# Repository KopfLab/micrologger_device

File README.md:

# *µLogger*

This repository holds the code, schematics, and documentation to build a ***M**odular **I**nternet **C**ontrollable **R**eal-time **O**ptical-density Logger* (***microLogger*** or ***µLogger*** for short). All content of this repository is free to use for noncommercial research and development efforts as outlined in the terms of the included [LICENSE file](LICENSE.md).

To cite ***µLogger*** in publications use:

> Kopf S and Younkin A, 2025. _µLogger: a Modular Internet Controllable Real-time Optical-density Logger_. <https://github.com/KopfLab/micrologger_device>

A BibTeX entry for LaTeX users is

```
@Manual{
  microLogger,
  title = {µLogger: a Modular Internet Controllable Real-time Optical-density Logger},
  author = {Sebastian Kopf and Adam Younkin},
  year = {2025},
  url = {https://github.com/KopfLab/micrologger_device}
}
```

## About

Modular Internet Controllable Real-time Optical-density Loggers (µLoggers) are optical density measurement devices for continuously recording the growth of a microbial culture directly in its culturing vessel. Each microLogger consists of a compact high strength carbon fibre culture vessel holder that has a built-in light source at a narrow band wavelength and a light sensor with automatically adjustable gain that measures the light transmission across the culture vessel to automatically and continuously quantify optical density at user defined time intervals. A magnetically coupled stirrer built into the vessel holder can agitate the culture both continuously as well as in vortexing mode  (= pulse agitation) at user-set stir/vortexing speeds from 50 to 5000 rpm. Culture vessel adapters that are magnetically secured to the vessel holder allow for quick and easy swapping for differently sized culture vessels and snugly hold the culture vessel in place using a radial spring mechanism. Adapters can be custom sized for the preferred culture vessel from standard 18mm diameter 15mL culture tubes up to 58mm GL45 100mL media bottles. Typical adapter sizes also cover culture vessels typically used in anaerobic microbial culture including balch tubes and serum bottles of varying sizes. Additional optional adapters that are magnetically secured on top of the vessel adapter can provide additional functionality such as user-controlled illumination for experiments with phototrophic microorganisms. Each µLogger is connected to a compact controller (the micrologger "brain") that connects to the culture vessel holder via a single cable such that the vessel holder can be placed inside an incubator (e.g. for temperature or gas modulation) while the controller sits outside the incubator and provides full control and power to the culture vessel holder for stirring, optical density measurements, and (optionally) lighting. The controller has built-in WiFi connectivity and receives/sends data wirelessly wirelessly. This makes it possible to monitor optical density of the microbial cultures in real-time from any location. The controller also has a built-in screen that displays the state of the micrologger (e.g. stir speed, read interval, internet connectivity) as well as the real-time data from the culture vessel so that users can check on their experiments with a glance at the controller without opening the incubator and without handling the culture vessel in any way to avoid potentially disturbing an experiment. For convenience, the controller can also be attached magnetically to the outside of the incubator (if metal) or any other metallic surface.

## Features

- **Continuous optical-density logging** — a narrow-band beam LED and an OPT101 photodetector with automatically optimized amplifier gain measure the light transmission across the culture vessel; the firmware computes optical density (−log₁₀ of transmittance) at user-defined intervals, propagates a standard-deviation error onto every reading, and stores the per-vessel zero reference on the device so it survives power outages.
- **Magnetic stirring & vortexing** — a built-in brushless motor drives a magnetically coupled stirrer with configurable speed, acceleration/deceleration ramps, and a vortex (pulse-agitation) mode; stirring can automatically pause or vortex around each optical-density read.
- **Swappable, magnetically secured vessel adapters** — 3D-printed adapters hold vessels from 18 mm / 15 mL culture tubes up to GL45 100 mL bottles (including Balch/Hungate tubes and serum bottles) with a radial spring mechanism, and accept stacking add-ons such as the illumination adapter.
- **Optional illumination for phototrophs** — a dimmable light adapter with permanent on/off or scheduled (repeating daily-cycle) operation and a light-synced cooling fan.
- **Temperature & power monitoring** — on-board TMP117 temperature sensing at the vessel holder plus supply-voltage monitoring with under-voltage warnings on the display.
- **At-a-glance local display** — the WiFi controller sits outside the incubator, links to the reader over a single cable, and shows live optical density, stir speed, temperature, connectivity, and publishing status on an OLED; it mounts magnetically to any metal surface.
- **Real-time cloud connectivity** — built on the Particle [Photon 2](https://docs.particle.io/reference/datasheets/wi-fi/photon-2-datasheet/); publishes JSON data logs via cloud webhooks (the `microloggerData` event) for recording into spreadsheets or databases, averages data over configurable intervals, and caches logs during offline periods to bridge device downtime.
- **Self-describing & remotely controllable** — the entire device state is exposed as a self-describing data structure (SDDS) that the [sddsParticle](https://github.com/KopfLab/sddsParticle) web GUI (or the Particle CLI/API) can browse and control, with persisted settings, one-shot actions, and per-variable publish intervals.
- **Open & modular** — component-based, easily extensible C++ firmware (separate `sensor`, `stirrer`, `lights`, and `environment` components), open [KiCad](https://www.kicad.org/) hardware, and open [OpenSCAD](https://openscad.org/) 3D-printable mechanical parts.

## Hardware

A µLogger is built from four custom circuit boards, designed in [KiCad](https://www.kicad.org/) with sources under [`pcbs/`](pcbs). For each board the board layout is shown below (click it to open the full schematic / wiring diagram as a PDF).

### Controller board — the µLogger "brain"

A Particle Photon 2 for WiFi and control, the OLED status display, the 24 V power input with supply-voltage monitoring, the controller-version code pins, and the single-cable connector to the reader (the vessel holder).

*→ [Controller board wiring diagram (PDF)](pcbs/controller_board/controller_board.pdf)*

### Sensor board

Mounted in the vessel holder: the OPT101 photodiode/transimpedance amplifier with a two-stage digital-potentiometer gain circuit (MCP4017 + AD5246), the TCA9534 I2C IO expander (reader-connection detection plus beam and indicator LEDs), and the measurement-beam LED. The board version is read back over the IO expander.

*→ [Sensor board wiring diagram (PDF)](pcbs/sensor_board/sensor_board.pdf)*

### LED board

The optional illumination adapter: the light LEDs driven by a PCA9633 PWM controller for dimming, together with the cooling fan.

*→ [LED board wiring diagram (PDF)](pcbs/led_board/led_board.pdf)*

### Temperature board

A simple TMP117 precision temperature sensor placed at the vessel holder.

*→ [Temperature board wiring diagram (PDF)](pcbs/temperature_board/temperature_board.pdf)*

## 3D printed parts

The vessel holder, stirrer, controller enclosure, and all vessel adapters are 3D-printable. The STL files live in [`prints/stl/`](prints/stl) and the parametric source models are the [OpenSCAD](https://openscad.org/) files [`prints/micrologger_device.scad`](prints/micrologger_device.scad) and [`prints/micrologger_controller.scad`](prints/micrologger_controller.scad). File names ending in `_nozzle_0.4mm` are optimized for a 0.4 mm printer nozzle.

The parts fall into a few groups:

- **Device body & stirrer** — the high-strength vessel-holder body (`micrologger_device_*`, designed to be printed in carbon-fibre-reinforced filament) that houses the sensor/beam optics, and the magnetically coupled `micrologger_stirrer_*`.
- **Vessel adapters** — magnetically secured, radially sprung adapters sized for specific culturing vessels: `balch`, `hungate`, `culture60`, `gl45`, `serum60`/`serum120`/`serum160`, plus the `base_*` adapters that go into the base of the vessel holder for small vial sizes.
- **Light adapters** — `micrologger_light_adapter_up`/`_down` for the optional illumination add-on.
- **Controller enclosure** — `micrologger_controller_body`, `micrologger_controller_back`, and `micrologger_controller_magnet_holder` for the "brain" controller box.

👉 See [**`prints/README.md`**](prints/README.md) for the complete list of all printable parts with rendered previews.

## Building, flashing & monitoring

The firmware is written for the Particle Photon 2 (platform `p2`) and built with the [Particle Cloud command line interface (CLI)](https://github.com/spark/particle-cli). Builds are driven by Ruby [Rake](https://ruby.github.io/rake/) (see [`particle_rake.rb`](particle_rake.rb), imported by the [`Rakefile`](Rakefile)) rather than `make`.

First-time setup:

- clone this repository **with submodules** (the `lib/` libraries are git submodules): `git clone --recurse-submodules ...`, or run `git submodule update --init --recursive` in an existing clone
- install the [Particle CLI](https://github.com/spark/particle-cli) and log into your account with `particle login`
- install the ruby gems with `bundle install`

Common Rake shortcuts (run `rake help` for the full list and `rake programs` for the list of compilable programs):

- `rake micrologger` — compile the main firmware in the Particle cloud (`bin/micrologger-p2-<version>-cloud.bin`)
- `rake local micrologger` — compile locally instead (requires the [Particle Workbench](https://docs.particle.io/getting-started/developer-tools/workbench/) local toolchain installed under `~/.particle`)
- `rake dev micrologger` — local compile + flash + watch sources and auto-recompile/-flash on change (via [Guard](Guardfile))
- `rake flash` — flash the newest binary in `bin/` to a USB-connected device (must be in DFU / blinking-yellow mode)
- `rake flash DEVICE=<name>` — flash the newest binary over-the-air via the cloud
- `rake monitor` — open the USB serial monitor
- targets chain, e.g. `rake micrologger flash monitor` compiles, flashes, then monitors

The `tests/` folder holds standalone test programs that build the same way (e.g. `rake blink`, `rake motor`). Which sources/libraries each program compiles is defined in its `.github/workflows/compile-<program>.yaml` file, which drives both local `rake` builds and continuous integration.

## Communicating with the device

The µLogger firmware is built on **self-describing data structures (SDDS)** using the [SDDS library](https://github.com/mLamneck/SDDS) and the [SDDS particleSpike](https://github.com/KopfLab/SDDS_particleSpike). The entire device — every setting, action, and live reading — is exposed as a single SDDS tree (see [The SDDS structure tree](#the-sdds-structure-tree) below).

The primary way to view and control a µLogger is the web-based [sddsParticle](https://github.com/KopfLab/sddsParticle) GUI, which reads a device's structure tree and automatically builds an editor for it. You can also interact with a device directly via the [Particle CLI](https://github.com/spark/particle-cli) (or the equivalent [Particle Cloud API](https://docs.particle.io/reference/api/) requests). All calls require being logged in (`particle login`) and only work for devices registered to your account.

**Reading the tree** (Particle cloud variables):

- `particle get <deviceID> getSddsValues` — the current values of all SDDS variables
- `particle get <deviceID> getSdds` — the full structure tree (types + values)
- `particle get <deviceID> getSddsSystem` — just the `SYSTEM` subtree
- `particle get <deviceID> getSddsCommandLog` — the log of recently received commands

**Setting variables / issuing commands** (Particle cloud function `sdds`): assign values with a `path=value` syntax where the path uses `.` as the separator. Issue several assignments at once by separating them with spaces:

```sh
particle call <deviceID> sdds "sensor.action=zero"
particle call <deviceID> sdds "stirrer.setpoint_rpm=500 stirrer.action=start"
particle call <deviceID> sdds "lights.action=schedule"
```

The return value is `0` when all assignments succeed. For a single failed assignment it is the negated error code (e.g. `-2` when the path could not be resolved); for a batch of assignments it is a bitmask flagging which ones failed. Special codes: `-200` = empty command, `-201` = more than 31 assignments in one call.

**Pushing data to the cloud on demand** (Particle cloud functions): `sendSdds`, `sendSddsValues`, and `sendSddsState` publish the structure tree, all values, or just the saveable state, respectively. Regular data logging is published on the **`microloggerData`** cloud event and configured through the `SYSTEM` structure (see the [SDDS particleSpike documentation](https://github.com/KopfLab/SDDS_particleSpike#the-system-structure)).

## The SDDS structure tree

Every µLogger exposes its complete state as an SDDS tree. Fields can be flagged as _read-only_ (reported by the device but not meant to be edited by the user) or _saveable_ (persisted across restarts, i.e. restored on boot and re-saved with the `SYSTEM` `saveState` action). Numeric fields carry their unit as a name suffix (e.g. `_ms`, `_sec`, `_rpm`, `_V`, `_C`, `_Ohm`, `_percent`, `_ppt` for parts-per-thousand ‰, `_dt` for a date/time, `_HHMM` for a 24h clock time). Actions are one-shot triggers that automatically reset to `___` (no action) after they run.

The top level of the tree contains the `SYSTEM` structure, the `device` connection flag, the four functional components (`sensor`, `stirrer`, `lights`, `environment`), and a low-level `HARDWARE` menu.

### SYSTEM

The `SYSTEM` structure is added automatically by the SDDS particleSpike and carries the device's identity, connection status, health/vitals, persisted-state handling, and all data recording/publishing settings. It is documented in full in the [SDDS particleSpike documentation](https://github.com/KopfLab/SDDS_particleSpike#the-system-structure).

### device

- **`device`** — _read-only_ — whether the controller (the "brain") is connected to the reader (the culture vessel holder) via RJ45 cable: `connected` or `disconnected` (detected via the reader's I2C bus).

### sensor

Optical-density measurement — the core function of the µLogger.

- **`action`** — trigger a one-off measurement action:
  - `zero`: establish the OD = 0 reference for the current culture vessel (typically done once before inoculation). If `gain.automatic` is `yes`, the gain is auto-optimized first, then paused for `gain.zeroPause_ms`, then the zero is recorded. The zero is persisted so it survives power outages.
  - `beamOn`: turn the measurement beam LED permanently on (e.g. to watch the live `reading.saturation_ppt`)
  - `beamOff`: turn the measurement beam off
  - `optimizeGain`: run the automatic amplifier-gain optimization to bring the signal to `gain.target_ppt`
  - `reset`: clear the zero reference and return to idle
- **`status`** — _read-only_ — `idle`, `reading`, `optimizing`, `waiting`, or `zeroing`
- **`reading`** — the latest measurement plus read timing/behavior settings
  - **`saturation_ppt`** — _read-only_ — the current live beam signal as a fraction of the ADC maximum, in ‰; watch this to avoid saturating the detector
  - **`readInterval_ms`** — _saveable_ — how often to take an OD reading (default: 2 minutes)
  - **`vortex`** — _saveable_ — vortex (pulse-agitate) the culture before each read (default: no)
  - **`stopStirrer`** — _saveable_ — stop the stirrer before each read (default: yes)
  - **`stopLights`** — _saveable_ — turn the light off during each read (default: yes)
  - **`wait_ms`** — _saveable_ — settling time after vortex/stirrer stop before reading (default: 0)
  - **`warmup_ms`** — _saveable_ — beam warm-up time whenever the beam turns on (default: 3000)
  - **`cooldown_ms`** — _saveable_ — wait after the beam turns off before reading the dark background (default: 500)
  - **`nextRead`** — _read-only_ — human-readable countdown to the next read
  - **`signal`** / **`signalSd`** — _read-only_ — mean and standard deviation of the beam (lit) signal of the last read
  - **`bgrd`** / **`bgrdSd`** — _read-only_ — mean and standard deviation of the dark-background signal of the last read
  - **`transmittance`** / **`transmittanceSd`** — _read-only_ — light transmittance relative to the zero reference, and its error
  - **`OD`** / **`ODSd`** — _read-only_ — optical density (−log₁₀ of transmittance) and its error
- **`zero`** — the zero reference, persisted so it survives power outages
  - **`last_dt`** — _read-only, saveable_ — timestamp of the last zeroing (`never` if never zeroed)
  - **`valid`** — _read-only, saveable_ — whether a valid zero exists; OD is only computed once this is `yes`
  - **`signal`** / **`signalSd`** — _read-only, saveable_ — beam signal (and SD) recorded at zeroing
  - **`bgrd`** / **`bgrdSd`** — _read-only, saveable_ — dark background (and SD) recorded at zeroing
- **`beam`** — the measurement-beam LED
  - **`status`** — _read-only_ — `on`, `off`, or `error`
  - **`error`** — _read-only_ — I2C error of the beam control
- **`gain`** — the signal amplifier gain
  - **`automatic`** — auto-optimize the gain before zeroing (default: yes; not persisted, so it must be re-enabled each session)
  - **`zeroPause_ms`** — _saveable_ — settling pause after automatic gain optimization before zeroing (default: 60000)
  - **`max_ppt`** — _read-only_ — the maximum attainable signal, in ‰
  - **`target_ppt`** — _saveable_ — target signal level for gain optimization, in ‰ (default: 920)
  - **`gain_Ohm`** — _read-only, saveable_ — the current total amplifier resistance (i.e. the gain), persisted across restarts
  - **`status`** — _read-only_ — `set` or `error`
  - **`error`** — _read-only_ — I2C error of the gain control
- **`error`** — _read-only_ — top-level OD error: `none`, `saturated`, `failedGain`, `failedZero`, or `failedRead`

### stirrer

The magnetically coupled stirrer built into the vessel holder.

- **`action`** — trigger a one-off stirrer action:
  - `start` / `stop`: turn continuous stirring on/off (also updates the persisted `state`)
  - `pause` / `resume`: temporarily stop/restart the motor **without** changing `state` (used internally during reads)
  - `vortex`: run a single vortex pulse — ramp up to `settings.vortexSpeed_rpm`, hold for `settings.vortexTime_sec`, then return to the previous speed
- **`state`** — _read-only, saveable_ — the persisted on/off intent of the stirrer (default: off)
- **`status`** — _read-only_ — `off`, `accelerating`, `decelerating`, `running`, or `error`
- **`error`** — _read-only_ — motor error
- **`event`** — _read-only_ — transient activity: `none`, `paused`, or `vortexing`
- **`setpoint_rpm`** — _saveable_ — target stir speed in rpm (default: 500)
- **`speed_rpm`** — _read-only_ — the measured actual speed in rpm
- **`settings`**
  - **`acceleration_rpm_s`** — _saveable_ — acceleration ramp in rpm per second (default: 500)
  - **`deceleration_rpm_s`** — _saveable_ — deceleration ramp in rpm per second (default: 3000)
  - **`maxSpeed_rpm`** — _saveable_ — maximum allowed speed (capped by the motor hardware limit)
  - **`vortexSpeed_rpm`** — _saveable_ — the speed of a vortex pulse (default: 3000)
  - **`vortexTime_sec`** — _saveable_ — how long to hold at vortex speed (default: 2)

### lights

The optional illumination adapter (for experiments with phototrophic microorganisms) and its cooling fan.

- **`action`** — trigger a one-off light action:
  - `on` / `off`: turn the light permanently on/off
  - `schedule`: run the light on a repeating on/off schedule (see the `schedule*` settings below)
  - `pause` / `resume`: temporarily turn the light off/back on without changing `state` (used during reads when `sensor.reading.stopLights` is yes)
- **`state`** — _read-only, saveable_ — the persisted light mode: `on`, `off`, or `schedule` (default: off)
- **`status`** — _read-only_ — the actual light output: `on`, `off`, or `error`
- **`event`** — _read-only_ — `none` or `paused`
- **`error`** — _read-only_ — I2C error of the light/fan driver
- **`intensity_percent`** — _saveable_ — light brightness, 1–100% (default: 100)
- **`scheduleOn_sec`** — _saveable_ — how long the light stays on per schedule cycle (default: 12 hours)
- **`scheduleOff_sec`** — _saveable_ — how long the light stays off per schedule cycle (default: 12 hours)
- **`scheduleOnStart_HHMM`** — _saveable_ — the time of day the on-phase begins, as a 24h `HHMM` value (default: 1200 = noon)
- **`scheduleInfo`** — _read-only_ — human-readable countdown to the next on/off switch
- **`fan`** — the cooling fan for the light adapter
  - **`action`** — `on`, `off`, or `withLight`
  - **`state`** — _read-only, saveable_ — the persisted fan mode: `on`, `off`, or `withLight` (run the fan only while the light is on) (default: withLight)
  - **`status`** — _read-only_ — `on`, `off`, or `error`

### environment

Temperature and supply-power monitoring.

- **`readInterval_ms`** — _saveable_ — how often to read the temperature sensor (default: 1000)
- **`temperature_C`** — _read-only_ — temperature measured at the vessel holder, in °C
- **`power_V`** — _read-only_ — supply voltage measured at the controller, in V
- **`powerReq_V`** — _saveable_ — the minimum required supply voltage; below this the display warns "not enough power" (default: 20.0)
- **`error`** — _read-only_ — I2C error of the temperature sensor

### HARDWARE

An advanced, low-level menu (added at the end of the tree) that exposes direct access to every peripheral — the I2C IO expander, the digital potentiometers and amplifier gain circuit, the OPT101 light sensor, the TMP117 temperature sensor, the supply-voltage divider, the PCA9633 light/fan PWM driver, the Nidec motor, the OLED display, and the detected controller/sensor PCB versions. It is intended for diagnostics and calibration only; the `sensor`, `stirrer`, `lights`, and `environment` components above are the normal interface.

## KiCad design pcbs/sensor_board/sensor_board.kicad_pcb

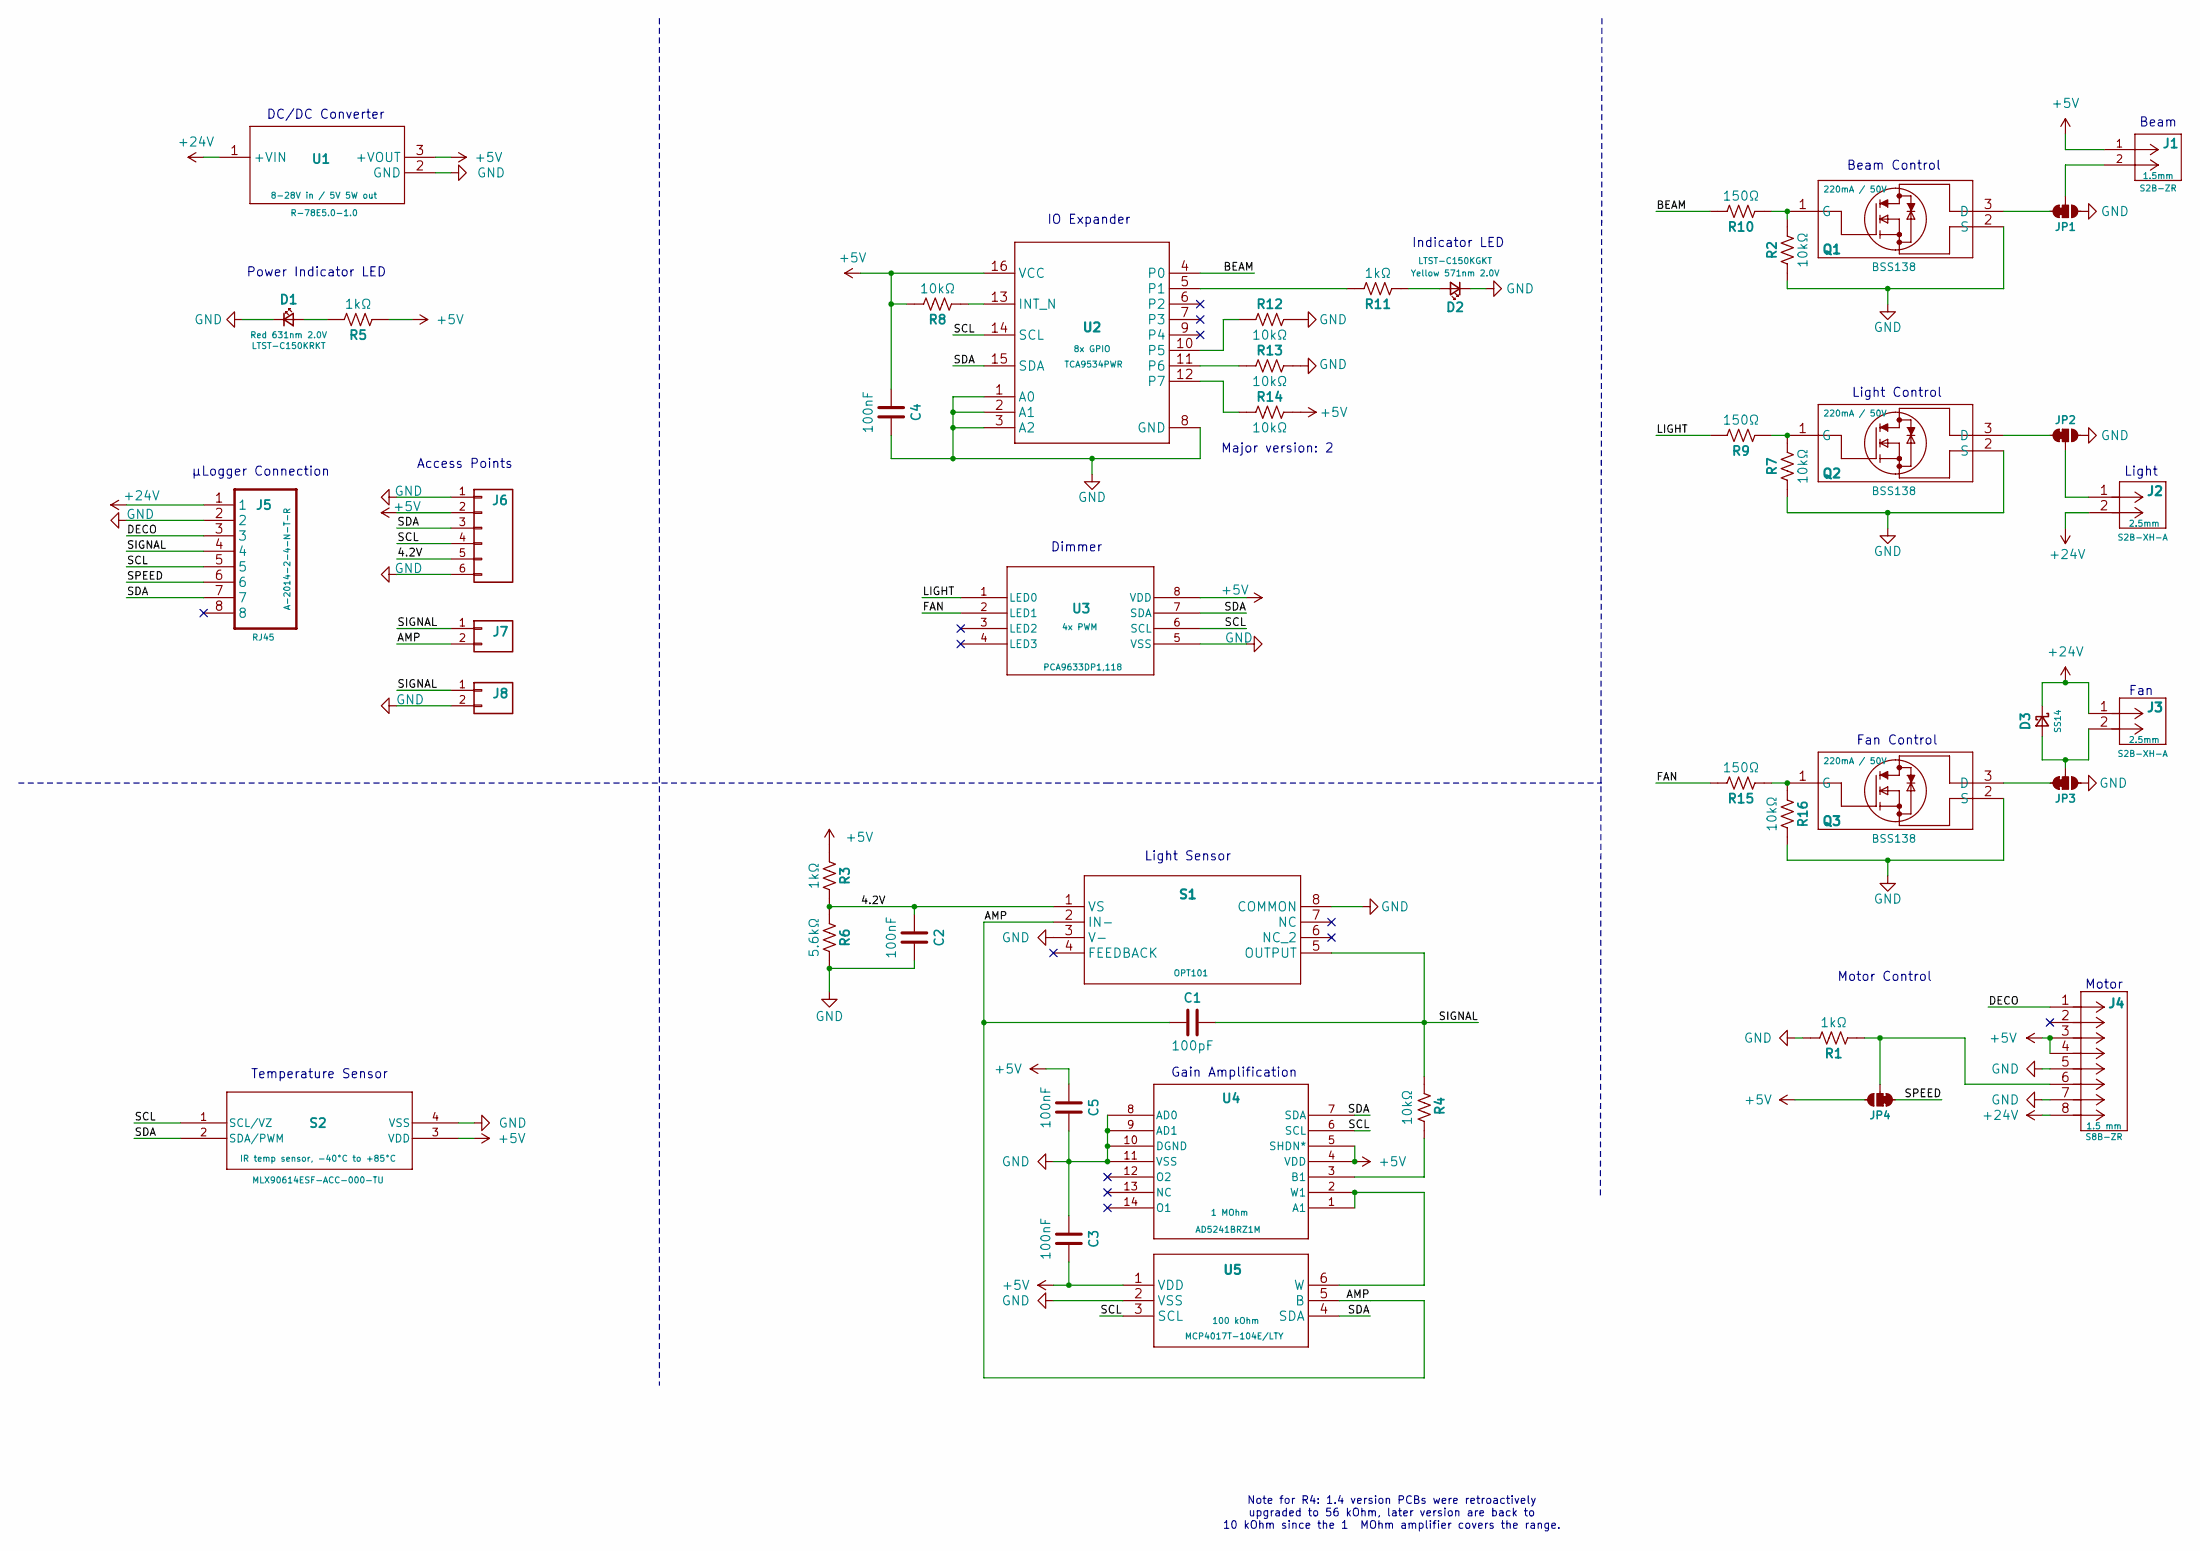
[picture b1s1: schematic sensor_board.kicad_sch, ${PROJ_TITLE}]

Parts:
C1: 100pF; C_0603; JLCPCB C14858
C2, C4: 100nF; C_0603; JLCPCB C1591
C3, C5: 100nF; C_0603
D1: Red 631nm 2.0V; LED_1206; MPN LTST-C150KRKT; DigiKey 160-1405-1-ND
D2: Yellow 571nm 2.0V; LED_1206; MPN LTST-C150KGKT; DigiKey 160-1404-1-ND
D3: 1A/40V/500mV; D_DO-214AC_SMA; MPN SS14; DigiKey SS14CT-ND
J1: 1.5mm; JST_ZH_2POS_RA; MPN S2B-ZR; DigiKey 455-1669-ND
J2, J3: 2.5mm; JST_XH_2POS_RA; MPN S2B-XH-A; DigiKey 455-S2B-XH-A-ND
J4: 1.5 mm; JST_ZR_8POS_RA; MPN S8B-ZR; DigiKey 455-S8B-ZR-ND
J5: RJ45; RJ45_A-2014-2-4-N-T-R; MPN A-2014-2-4-N-T-R; DigiKey AE10396-ND
J6: Conn_01x06; PIN_HEADERS_1X06
J7, J8: Conn_01x02; PIN_HEADERS_1X02
JP1, JP2, JP3, JP4: Jumper_3_NC-1_Trace
Q1, Q2, Q3: 220mA / 50V; SOT-23-3; MPN BSS138; DigiKey BSS138CT-ND
R1, R5, R11: 1kΩ; R_0603
R2, R7, R12, R13, R14, R16: 10kΩ; R_0603
R3: 1kΩ; R_0603; JLCPCB C118155
R4: 10kΩ; R_1206; JLCPCB C17902
R6: 5.6kΩ; R_0603; JLCPCB C403276
R8: 10kΩ; R_0603; JLCPCB C191124
R9, R15: 150Ω; R_0603
R10: 150Ω; R_0603; JLCPCB C400650
S1: Value; OPT101; MPN OPT101; DigiKey 296-23090-5-ND
S2: IR temp sensor, -40°C to +85°C; MLX90614; MPN MLX90614ESF-ACC-000-TU; DigiKey MLX90614ESF-ACC-000-TU-ND
U1: 8-28V in / 5V 5W out; DC_DC_converter_R-78E5.0-1.0; MPN R-78E5.0-1.0; DigiKey 945-2201-ND
U2: 8x GPIO; SOT-403-1_TSSOP16; MPN TCA9534PWR; DigiKey 296-40574-1-ND
U3: 4x PWM; SOT-505-1_TSSOP8; MPN PCA9633DP1,118; DigiKey 568-3236-1-ND
U4: 1 MOhm; 14-SOIC; MPN AD5241BRZ1M; DigiKey 505-AD5241BRZ1M-ND
U5: 100 kOhm; SOT-363_TSSOP6_SC88; MPN MCP4017T-104E/LTY; DigiKey 150-MCP4017T-104E/LTYCT-ND

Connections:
+5V: C3.2, C4.1, C5.1, J1.1, J4.3, J4.4, J6.2, JP4.3 (C), R3.1, R5.1, R8.2, R14.2, S2.3 (VDD), U1.3 (+VOUT), U2.16 (VCC), U3.8 (VDD), U4.4 (VDD), U4.5 (SHDN*), U5.1 (VDD)
+24V: D3.1 (K), J2.2, J3.1, J4.8, J5.1, U1.1 (+VIN)
/4.2V: C2.1, J6.5, R3.2, R6.1, S1.1 (VS)
/AMP: C1.1, J7.2, S1.2 (IN-), U5.5 (B)
/BEAM: R10.2, U2.4 (P0)
/DECO: J4.1, J5.3
/FAN: R15.2, U3.2 (LED1)
/LIGHT: R9.2, U3.1 (LED0)
/SCL: J5.5, J6.4, S2.1 (SCL/VZ), U2.14 (SCL), U3.6 (SCL), U4.6 (SCL), U5.3 (SCL)
/SDA: J5.7, J6.3, S2.2 (SDA/PWM), U2.15 (SDA), U3.7 (SDA), U4.7 (SDA), U5.4 (SDA)
/SIGNAL: C1.2, J5.4, J7.1, J8.1, R4.1, S1.5 (OUTPUT)
/SPEED: J5.6, JP4.1 (A)
GND: C2.2, C3.1, C4.2, C5.2, D1.1 (K), D2.1 (K), J4.5, J4.7, J5.2, J6.1, J6.6, J8.2, JP1.3 (C), JP2.3 (C), JP3.3 (C), Q1.2 (S), Q2.2 (S), Q3.2 (S), R1.2, R2.1, R6.2, R7.1, R12.2, R13.2, R16.2, S1.3 (V-), S1.8 (COMMON), S2.4 (VSS), U1.2 (GND), U2.1 (A0), U2.2 (A1), U2.3 (A2), U2.8 (GND), U3.5 (VSS), U4.8 (AD0), U4.9 (AD1), U4.10 (DGND), U4.11 (VSS), U5.2 (VSS)
unnamed: D1.2 (A), R5.2
unnamed: D2.2 (A), R11.1
unnamed: D3.2 (A), J3.2, JP3.2 (B)
unnamed: JP1.1 (A), Q1.3 (D)
unnamed: J1.2, JP1.2 (B)
unnamed: JP2.1 (A), Q2.3 (D)
unnamed: J2.1, JP2.2 (B)
unnamed: JP3.1 (A), Q3.3 (D)
unnamed: J4.6, JP4.2 (B), R1.1
unnamed: Q1.1 (G), R2.2, R10.1
unnamed: Q2.1 (G), R7.2, R9.1
unnamed: Q3.1 (G), R15.1, R16.1
unnamed: R8.1, U2.13 (INT_N)
unnamed: R11.2, U2.5 (P1)
unnamed: R12.1, U2.10 (P5)
unnamed: R13.1, U2.11 (P6)
unnamed: R14.1, U2.12 (P7)
unnamed: U4.1 (A1), U4.2 (W1), U5.6 (W)
unnamed: R4.2, U4.3 (B1)

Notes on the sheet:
Light Sensor
Fan Control
Note for R4: 1.4 version PCBs were retroactively upgraded to 56 kOhm, later version are back to 10 kOhm since the 1 MOhm amplifier covers the range.
Gain Amplification
IO Expander
Motor Control
Light Control
Light
Access Points
Dimmer
Fan
DC/DC Converter
Beam Control
Motor
Temperature Sensor
Indicator LED
µLogger Connection
Power Indicator LED
Beam
Major version: 2

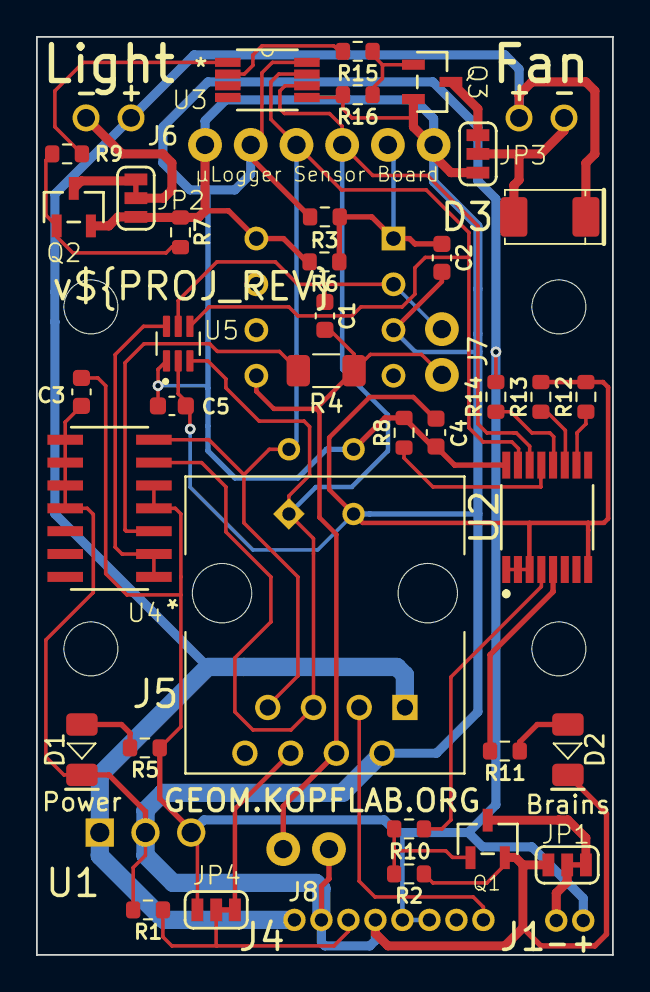
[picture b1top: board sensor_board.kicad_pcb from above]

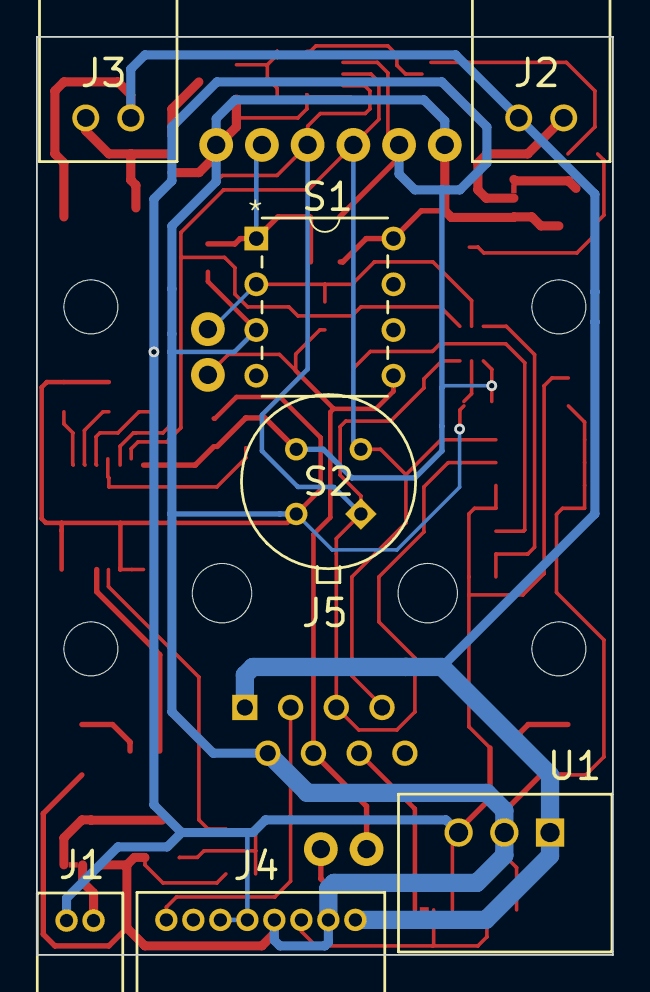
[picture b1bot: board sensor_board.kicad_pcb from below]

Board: 2 copper layers, 32.0 x 51.0 mm, 46 parts (7 on the bottom side), 32 nets.

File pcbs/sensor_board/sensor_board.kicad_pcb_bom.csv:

Designator,Quantity,Value,Footprint,Package,MPN,DNP,Mount_Type,Description,JLCPCB,JLCPCBURL,DigiKey,DigiKeyURL
C1,1,100pF,C_0603,,,,smt,Unpolarized capacitor,C14858,https://jlcpcb.com/partdetail/15530-CL10C101JB8NNNC/C14858,,
"C2, C3, C4, C5",4,100nF,C_0603,,,,smt,Unpolarized capacitor,C1591,https://jlcpcb.com/partdetail/1943-CL10B104KB8NNNC/C1591,,
D1,1,Red 631nm 2.0V,LED_1206,,LTST-C150KRKT,,smt,Red 631nm LED Indication - Discrete 2V 1206 (3216 Metric),C125086,https://jlcpcb.com/partdetail/LiteOn-LTSTC150KRKT/C125086,160-1405-1-ND,https://www.digikey.com/en/products/detail/liteon/LTST-C150K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
D2,1,Yellow 571nm 2.0V,LED_1206,,LTST-C150KGKT,,smt,Green 571nm LED Indication - Discrete 2V 1206 (3216 Metric),C125085,https://jlcpcb.com/partdetail/LiteOn-LTSTC150KGKT/C125085,160-1404-1-ND,https://www.digikey.com/en/products/detail/liteon/LTST-C150K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
D3,1,1A/40V/500mV,D_DO-214AC_SMA,,SS14,,smt,Diode 40 V 1A Surface Mount DO-214AC (SMA),C83852,https://jlcpcb.com/partdetail/onsemi-SS14/C83852,SS14CT-ND,https://www.digikey.com/en/products/detail/onsemi/SS14/965474
J1,1,1.5mm,JST_ZH_2POS_RA,,S2B-ZR,,tht,"Connector Header Through Hole, Right Angle 2 position 0.059"" (1.50mm)",,,455-1669-ND,https://www.digikey.com/en/products/detail/jst-sales-america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
"J2, J3",2,2.5mm,JST_XH_2POS_RA,,S2B-XH-A,,tht,"Connector Header Through Hole, Right Angle 2 position 0.098"" (2.50mm)",,,455-S2B-XH-A-ND,https://www.digikey.com/en/products/detail/jst-sales-america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
J4,1,1.5 mm,JST_ZR_8POS_RA,,S8B-ZR,,tht,"Connector Header Through Hole, Right Angle 8 position 0.059"" (1.50mm)",,,455-S8B-ZR-ND,https://www.digikey.com/en/products/detail/jst-sales-america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
J5,1,RJ45,RJ45_A-2014-2-4-N-T-R,,A-2014-2-4-N-T-R,,tht,"Jack Modular Connector 8p8c (RJ45, Ethernet) Vertical Unshielded",,,AE10396-ND,https://www.digikey.com/en/products/detail/assmann-wsw-compo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
J6,1,Conn_01x06,PIN_HEADERS_1X06,,,,tht,"Basic 0.1"" PTH",,,,
"J7, J8",2,Conn_01x02,PIN_HEADERS_1X02,,,,tht,"Basic 0.1"" PTH",,,,
"JP1, JP2, JP3, JP4",4,~,Jumper_3_NC-1_Trace,,,,tht,"3-pole Solder Jumper, pins 1+2 closed/bridged",,,,
"Q1, Q2, Q3",3,220mA / 50V,SOT-23-3,,BSS138,,tht,N-Channel 50 V 2200mA 350mW (Ta) Surface Mount SOT-23-3,C52895,https://jlcpcb.com/partdetail/onsemi-BSS138/C52895,BSS138CT-ND,https://www.digikey.com/en/products/detail/onsemi/BSS138/244210
"R1, R11, R3, R5",4,1kΩ,R_0603,,,,smt,"Resistor, US symbol",C118155,https://jlcpcb.com/partdetail/PANASONIC-ERJ3EKF1001V/C118155,,
"R10, R15, R9",3,150Ω,R_0603,,,,smt,"Resistor, US symbol",C400650,https://jlcpcb.com/partdetail/PANASONIC-ERJ3EKF1500V/C400650,,
"R12, R13, R14, R16, R2, R7, R8",7,10kΩ,R_0603,,,,smt,"Resistor, US symbol",C191124,https://jlcpcb.com/partdetail/PANASONIC-ERJ3EKF1002V/C191124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,,
R4,1,10kΩ,R_1206,,,,smt,"Resistor, US symbol",C17902,https://jlcpcb.com/partdetail/18590-1206W4F1002T5E/C17902,,
R6,1,5.6kΩ,R_0603,,,,smt,"Resistor, US symbol",C403276,https://jlcpcb.com/partdetail/PANASONIC-ERJ3EKF5601V/C403276,,
S1,1,Value,OPT101,,OPT101,,tht,"Optical Sensor Ambient 650nm Voltage 8-DIP (0.300"", 7.62mm)",,,296-23090-5-ND,https://www.digikey.com/en/products/detail/texas-instruments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
S2,1,"IR temp sensor, -40°C to +85°C",MLX90614,,MLX90614ESF-ACC-000-TU,,tht,"Temperature Sensor Digital, Infrared (IR) -40°C ~ 85°C 16 b TO-39, 5V",,,MLX90614ESF-ACC-000-TU-ND,https://www.digikey.com/en/products/detail/melexis-technolog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
U1,1,8-28V in / 5V 5W out,DC_DC_converter_R-78E5.0-1.0,,R-78E5.0-1.0,,tht,Linear Regulator Replacement DC DC Converter 1 Output 5V 1A 8V - 28V Input,,,945-2201-ND,https://www.digikey.com/en/products/detail/recom-power/R-78E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
U2,1,8x GPIO,SOT-403-1_TSSOP16,,TCA9534PWR,,tht,I/O Expander 8 I2C 400 kHz 16-TSSOP,C783615,https://jlcpcb.com/partdetail/TexasInstruments-TCA9534PWR/C783615,296-40574-1-ND,https://www.digikey.com/en/products/detail/texas-instruments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
U3,1,4x PWM,SOT-505-1_TSSOP8,,"PCA9633DP1,118",,smt,LED Driver IC 4 Output Power Switch I2C Dimming 25mA 8-TSSOP,C88381,https://jlcpcb.com/partdetail/NXPSemicon-PCA9633DP1118/C8838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,568-3236-1-ND,https://www.digikey.com/en/products/detail/nxp-usa-inc/PCA96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
U4,1,1 MOhm,14-SOIC,,AD5241BRZ1M,,smt,Digital Potentiometer 1M Ohm 1 Circuit 256 Taps I2C Interface 14-SOIC,C649389,https://jlcpcb.com/partdetail/AnalogDevices-AD5241BRZ1M/C649389,505-AD5241BRZ1M-ND,https://www.digikey.com/en/products/detail/analog-devices-in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
U5,1,100 kOhm,SOT-363_TSSOP6_SC88,,MCP4017T-104E/LTY,,smt,Digital Potentiometer 100k Ohm 1 Circuit 128 Taps I2C Interface SC-70-6,C510890,https://jlcpcb.com/partdetail/MicrochipTech-MCP4017T_104ELT/C510890,150-MCP4017T-104E/LTYCT-ND,https://www.digikey.com/en/products/detail/microchip-technol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

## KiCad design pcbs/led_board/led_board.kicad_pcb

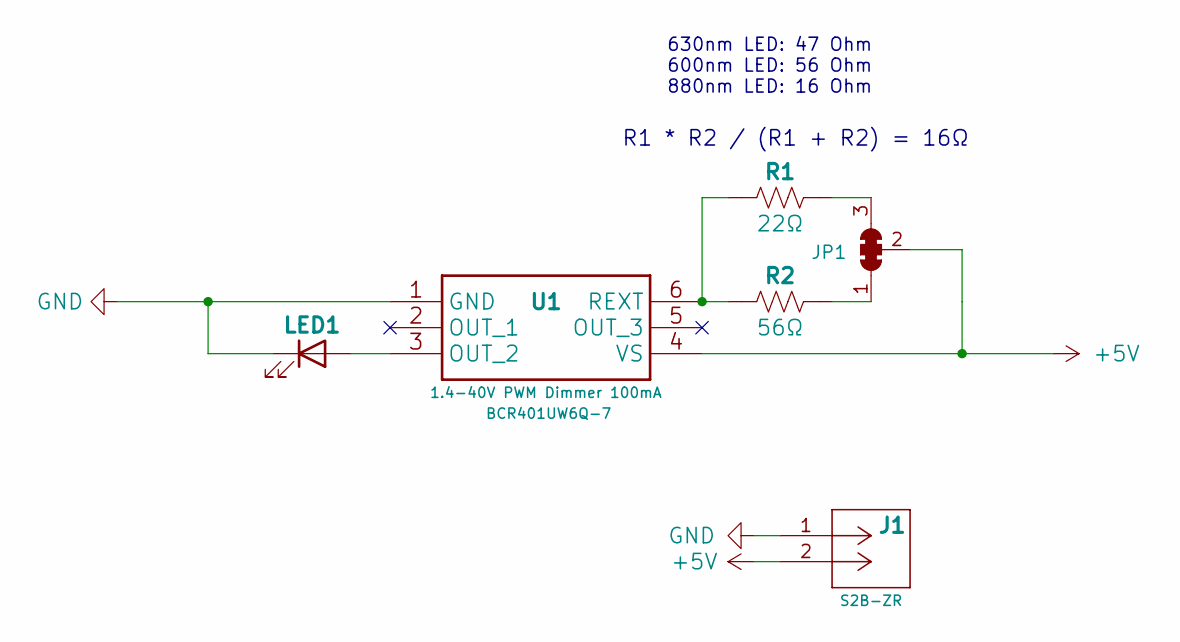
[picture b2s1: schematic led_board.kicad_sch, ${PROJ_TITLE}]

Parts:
J1: CONN HEADER R/A 2POS 1.5MM; JST_ZH_2POS_RA; MPN S2B-ZR; DigiKey 455-1669-ND
JP1: SolderJumper_3_Bridged123; SolderJumper3_Bridged
LED1: 630nm 1.9V 50mA; TO-46-2; MPN MTE7063NK2-UR; DigiKey 1125-1382-ND
R1: 22Ω; R_1206; JLCPCB C17958
R2: 56Ω; R_1206; JLCPCB C17995
U1: 1.4-40V PWM Dimmer 100mA; SOT-23-6; MPN BCR401UW6Q-7; DigiKey BCR401UW6Q-7DICT-ND

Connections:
+5V: J1.2, JP1.2 (C), U1.4 (VS)
GND: J1.1, LED1.1 (K), U1.1 (GND)
unnamed: JP1.1 (A), R2.2
unnamed: JP1.3 (B), R1.2
unnamed: LED1.2 (A), U1.3 (OUT_2)
unnamed: R1.1, R2.1, U1.6 (REXT)

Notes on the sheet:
R1 * R2 / (R1 + R2) = 16Ω
630nm LED: 47 Ohm 600nm LED: 56 Ohm 880nm LED: 16 Ohm

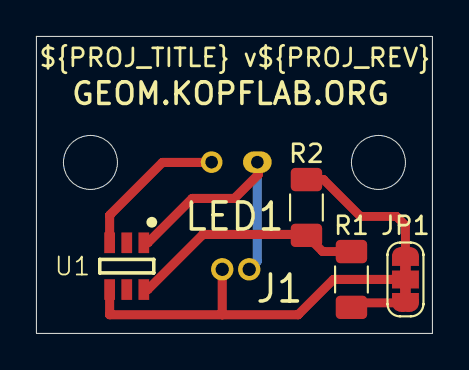
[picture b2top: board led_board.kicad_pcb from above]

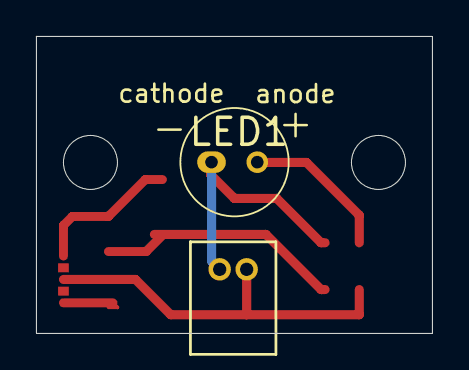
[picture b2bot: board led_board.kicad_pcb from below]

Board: 2 copper layers, 22.0 x 16.5 mm, 6 parts (2 on the bottom side), 6 nets.

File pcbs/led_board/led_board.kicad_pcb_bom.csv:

Designator,Quantity,Value,Footprint,Package,MPN,DNP,Mount_Type,Description,DigiKey,DigiKeyURL,Sim.Pins,URL,JLCPCB,JLCPCBURL,FP_Status
J1,1,CONN HEADER R/A 2POS 1.5MM,JST_ZH_2POS_RA,,S2B-ZR,,tht,"Connector Header Through Hole, Right Angle 2 position 0.059"" (1.50mm)",455-1669-ND,https://www.digikey.com/en/products/detail/jst-sales-america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,,,,,
LED1,1,630nm 1.9V 50mA,TO-46-2,,MTE7063NK2-UR,,tht,Visible Emitter 630nm 1.9V 50mA 5° TO-46-2 Lens Top Metal Can,1125-1382-ND,https://www.digikey.com/en/products/detail/marktech-optoelec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,1=K 2=A,https://www.digikey.com/en/products/detail/marktech-optoelec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,,,
R1,1,22Ω,R_1206,,,,smt,"Resistor, US symbol",,,,,C17958,https://jlcpcb.com/partdetail/18646-1206W4F220JT5E/C17958,
R2,1,56Ω,R_1206,,,,smt,"Resistor, US symbol",,,,,C17995,https://jlcpcb.com/partdetail/18683-1206W4F560JT5E/C17995,done
U1,1,1.4-40V PWM Dimmer 100mA,SOT-23-6,,BCR401UW6Q-7,,tht,LED Driver IC 1 Output Linear PWM Dimming 100mA SOT-26,BCR401UW6Q-7DICT-ND,https://www.digikey.com/en/products/detail/diodes-incorporat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,,https://www.digikey.com/en/products/detail/diodes-incorporat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,C2678813,https://jlcpcb.com/partdetail/DiodesIncorporated-BCR401UW6Q7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,

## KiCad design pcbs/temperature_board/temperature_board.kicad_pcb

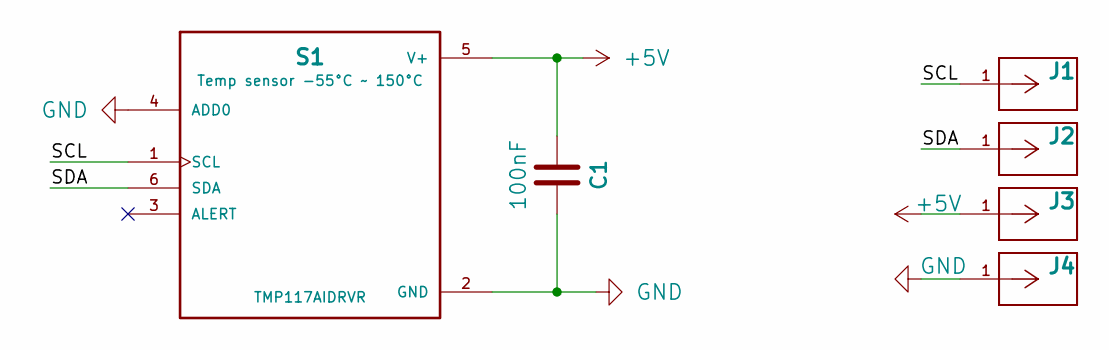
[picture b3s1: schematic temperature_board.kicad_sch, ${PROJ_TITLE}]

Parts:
C1: 100nF; C_0603; JLCPCB C1591
J1: SCL; PIN_HEADERS_1X01
J2: SDA; PIN_HEADERS_1X01
J3: +5V; PIN_HEADERS_1X01
J4: GND; PIN_HEADERS_1X01
S1: Temp sensor -55°C ~ 150°C; WSON-6_2x2mm_nopad; MPN TMP117AIDRVR; DigiKey 296-51834-1-ND

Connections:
+5V: C1.1, J3.1, S1.5 (V+)
/SCL: J1.1, S1.1 (SCL)
/SDA: J2.1, S1.6 (SDA)
GND: C1.2, J4.1, S1.2 (GND), S1.4 (ADD0)

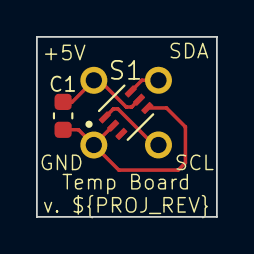
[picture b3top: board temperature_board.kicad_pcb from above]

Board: 2 copper layers, 10.0 x 10.0 mm, 6 parts (0 on the bottom side), 4 nets.

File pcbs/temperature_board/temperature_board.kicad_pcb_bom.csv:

Designator,Quantity,Value,Footprint,Package,MPN,DNP,Mount_Type,Description,JLCPCB,JLCPCBURL,STANDARD,DigiKey,DigiKeyURL
C1,1,100nF,C_0603,,,,smt,Unpolarized capacitor,C1591,https://jlcpcb.com/partdetail/1943-CL10B104KB8NNNC/C1591,,,
J1,1,SCL,PIN_HEADERS_1X01,,,,tht,,,,,,
J2,1,SDA,PIN_HEADERS_1X01,,,,tht,,,,,,
J3,1,+5V,PIN_HEADERS_1X01,,,,tht,,,,,,
J4,1,GND,PIN_HEADERS_1X01,,,,tht,,,,,,
S1,1,Temp sensor -55°C ~ 150°C,WSON-6_2x2mm_nopad,,TMP117AIDRVR,,smt,"Temperature Sensor Digital, Local -55°C ~ 150°C 16 b 6-WSON (2x2)",C699536,https://jlcpcb.com/partdetail/TexasInstruments-TMP117AIDRVR/C699536,IPC 7351B,296-51834-1-ND,https://www.digikey.com/en/products/detail/texas-instruments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

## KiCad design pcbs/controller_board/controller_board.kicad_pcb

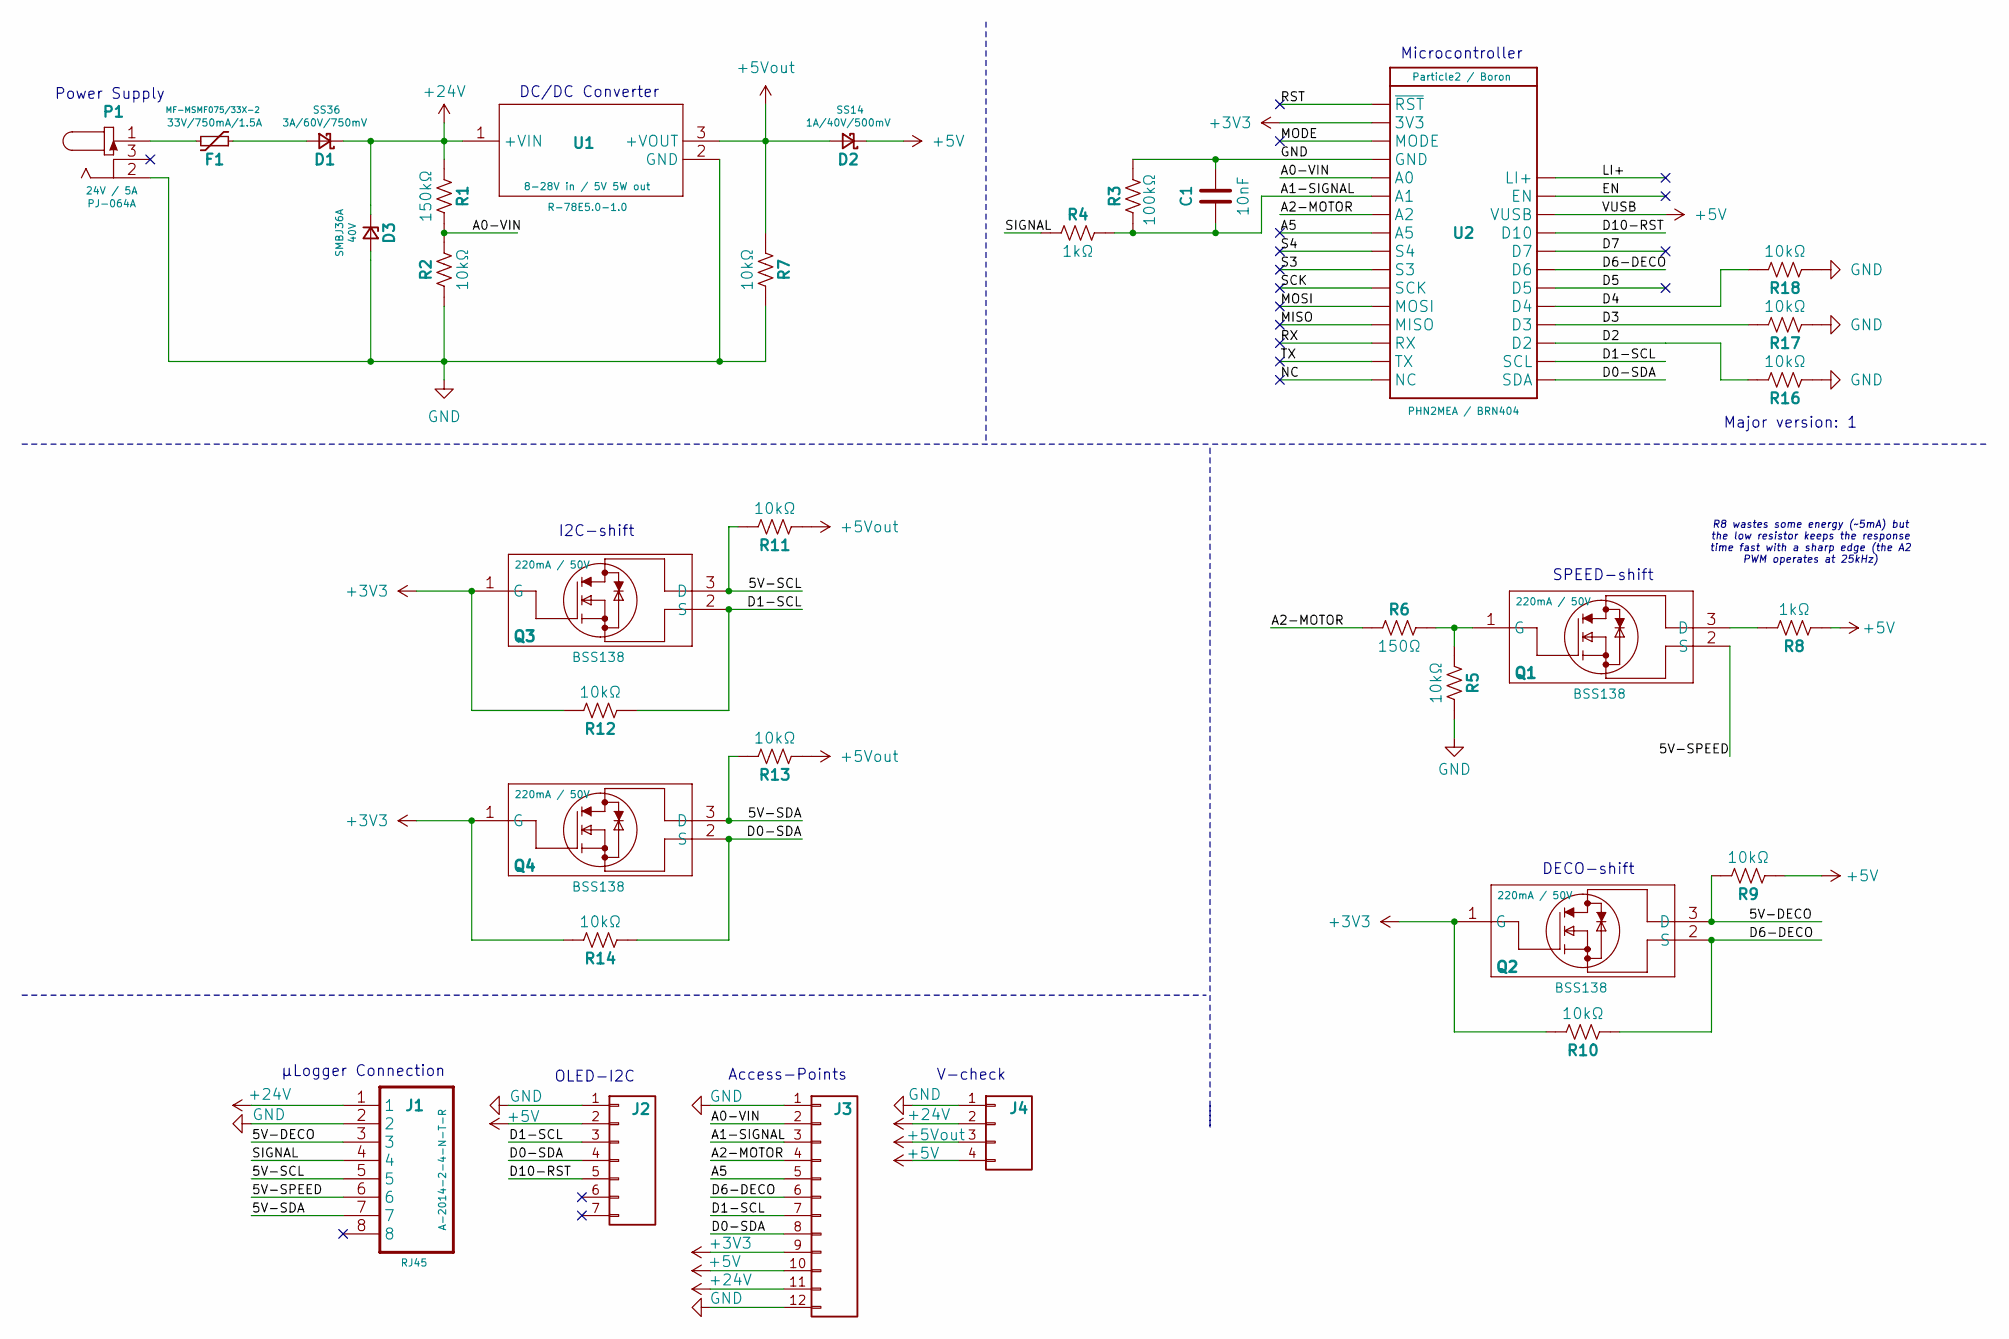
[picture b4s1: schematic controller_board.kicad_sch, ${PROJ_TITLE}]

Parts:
C1: 10nF; C_0603; JLCPCB C1589
D1: 3A/60V/750mV; D_DO-214AB_SMC; MPN SS36; DigiKey SS36FSCT-ND
D2: 1A/40V/500mV; D_DO-214AC_SMA; MPN SS14; DigiKey SS14CT-ND
D3: 40V; D_DO-214AA_SMB; MPN SMBJ36A; DigiKey SMBJ36ALFCT-ND
F1: 33V/750mA/1.5A; Fuse_1812; MPN MF-MSMF075/33X-2; DigiKey 118-MF-MSMF075/33X-2CT-ND
J1: RJ45; RJ45_A-2014-2-4-N-T-R; MPN A-2014-2-4-N-T-R; DigiKey AE10396-ND
J2: Conn_01x07; PIN_HEADERS_1X07
J3: Conn_01x12; PIN_HEADERS_1X12
J4: PINHD-1X4; PIN_HEADERS_1X04
P1: 24V / 5A; PWR_JACK_PJ-064A; MPN PJ-064A; DigiKey CP-064A-ND
Q1, Q2, Q3, Q4: 220mA / 50V; SOT-23-3; MPN BSS138; DigiKey BSS138CT-ND
R1: 150kΩ; R_1206; JLCPCB C17916
R2, R7, R9, R10, R11, R12, R13, R14, R16, R17, R18: 10kΩ; R_1206
R3: 100kΩ; R_1206; JLCPCB C17900
R4: 1kΩ; R_1206
R5: 10kΩ; R_1206; JLCPCB C17902
R6: 150Ω; R_1206; JLCPCB C17917
R8: 1kΩ; R_1206; JLCPCB C4410
U1: 8-28V in / 5V 5W out; DC_DC_converter_R-78E5.0-1.0; MPN R-78E5.0-1.0; DigiKey 945-2201-ND
U2: Particle2 / Boron; PHOTON2; MPN PHN2MEA / BRN404

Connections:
+3V3: J3.9, Q2.1 (G), Q3.1 (G), Q4.1 (G), R10.2, R12.2, R14.2, U2.2 (3V3)
+5V: D2.1 (K), J2.2, J3.10, J4.4, R8.1, R9.1, U2.26 (VUSB)
+5Vout: D2.2 (A), J4.3, R7.1, R11.1, R13.1, U1.3 (+VOUT)
+24V: D1.1 (K), D3.1 (K), J1.1, J3.11, J4.2, R1.1, U1.1 (+VIN)
/5V-DECO: J1.3, Q2.3 (D), R9.2
/5V-SCL: J1.5, Q3.3 (D), R11.2
/5V-SDA: J1.7, Q4.3 (D), R13.2
/5V-SPEED: J1.6, Q1.2 (S)
/A0-VIN: J3.2, R1.2, R2.2, U2.5 (A0)
/A1-SIGNAL: C1.1, J3.3, R3.1, R4.2, U2.6 (A1)
/A2-MOTOR: J3.4, R6.1, U2.7 (A2)
/A5: J3.5, U2.8 (A5)
/D0-SDA: J2.4, J3.8, Q4.2 (S), R14.1, U2.17 (SDA)
/D1-SCL: J2.3, J3.7, Q3.2 (S), R12.1, U2.18 (SCL)
/D2: R16.2, U2.19 (D2)
/D3: R17.2, U2.20 (D3)
/D4: R18.2, U2.21 (D4)
/D5: U2.22 (D5)
/D6-DECO: J3.6, Q2.2 (S), R10.1, U2.23 (D6)
/D7: U2.24 (D7)
/D10-RST: J2.5, U2.25 (D10)
/EN: U2.27 (EN)
/LI+: U2.28 (LI+)
/MISO: U2.13 (MISO)
/MODE: U2.3 (MODE)
/MOSI: U2.12 (MOSI)
/NC: U2.16 (NC)
/RST: U2.1 (~RST)
/RX: U2.14 (RX)
/S3: U2.10 (S3)
/S4: U2.9 (S4)
/SCK: U2.11 (SCK)
/SIGNAL: J1.4, R4.1
/TX: U2.15 (TX)
GND: C1.2, D3.2 (A), J1.2, J2.1, J3.1, J3.12, J4.1, P1.2, R2.1, R3.2, R5.2, R7.2, R16.1, R17.1, R18.1, U1.2 (GND), U2.4 (GND)
unnamed: D1.2 (A), F1.1
unnamed: F1.2, P1.1
unnamed: Q1.3 (D), R8.2
unnamed: Q1.1 (G), R5.1, R6.2

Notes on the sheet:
Major version: 1
µLogger Connection
Microcontroller
R8 wastes some energy (~5mA) but the low resistor keeps the response time fast with a sharp edge (the A2 PWM operates at 25kHz)
SPEED-shift
Power Supply
DC/DC Converter
Access-Points
V-check
DECO-shift
I2C-shift
OLED-I2C

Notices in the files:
pcbs/controller_board/controller_board.kicad_sch:
https://creativecommons.org/licenses/by-sa/4.0
Released under the Creative Commons Share-Alike 4.0 License
